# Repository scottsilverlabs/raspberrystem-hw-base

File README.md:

raspberrystem-hw-base
=====================

raspberrySTEM(TM) base hardware schematics and related documents

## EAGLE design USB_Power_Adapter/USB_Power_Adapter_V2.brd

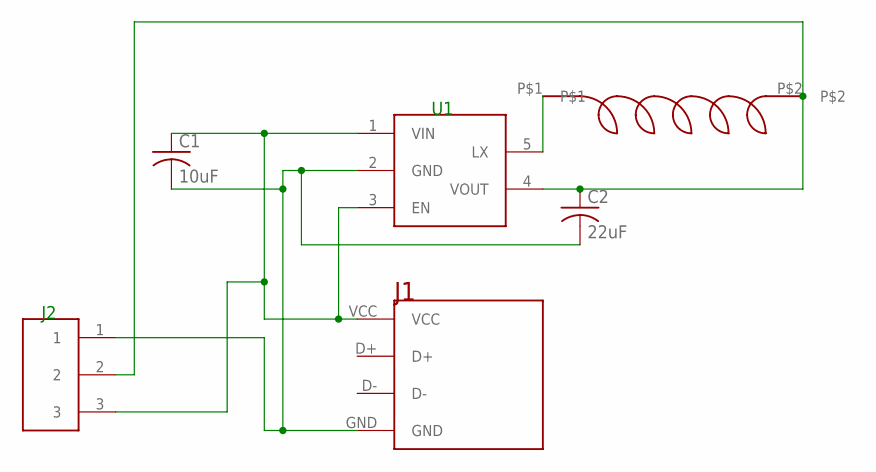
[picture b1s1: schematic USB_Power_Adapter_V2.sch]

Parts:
C1: 10uF; C0805K
C2: 22uF; C0805K
J1: MICROUSBMICROUSB_THRU; MICROUSB_THRU
U1: SC189
U$1: SMDINDUCTOR
U$2: DF3_1X3

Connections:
GND: C1.2, C2.2, J1.GND, U1.2 (GND), U$2.1
L: U1.5 (LX), U$1.P$1
VIN: C1.1, J1.VCC, U1.1 (VIN), U1.3 (EN), U$2.3
VOUT: C2.1, U1.4 (VOUT), U$1.P$2, U$2.2

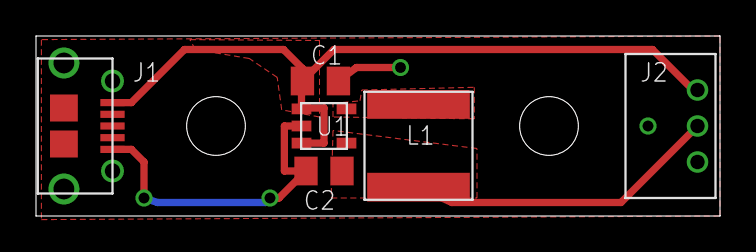
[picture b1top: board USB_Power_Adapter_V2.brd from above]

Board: 2 copper layers, 38.0 x 10.0 mm, 6 parts (0 on the bottom side), 4 nets.

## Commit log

2014-06-06 Added AL License to all applicable files
2014-06-17 Added schematics, gerber files, and BOM for USB Power Adapter
2014-06-18 Initial rev of case (pulled from dropbox rev8 dev)
2014-06-19 Forced name U1
2014-06-19 Fixed junctions
2014-06-25 Updates for new power and connector PCBs, and other fixes
    - Fastex clip broke - reinforce
    - Epilog still has artifact where Battery strap arrows are cut instead
    of just etched
    - Add more space to get battery strap on?
    - Adjust battery strap width? (0.3"?)
    - Move RasPi box etching ~1/64" to the right
2014-06-25 Added mounting holes, changed all screws to 5/8"
2014-06-25 Modified speaker, Lid connector PCB, screws
    Old speaker holes hit speaker diaphragm, new holes shouldn’t
    (untested). Added Custom Lid Connector PCB holes. Changed all screws
    to use #4-40, 5/8”
2014-06-25 Added USB power adapter files
2014-07-07 Added parts library
2014-07-24 Decreased and changed "Battery Strap" font, removed "Breadboards"
2014-07-24 Fixed broken line width/color
2014-07-24 Added new logo and text
2014-07-24 Changed spacing and clearance for USB Power Adapter PCB
2014-07-25 Removed old usb power adapter Gerber files and move L1 text
2014-07-26 Base acrylic: USB power adapter
    Increased USB power adapter top screw hole to oval to accommodate both
    board versions (2 places)
    Removed J from USB power spacer for Model B plus compatibility
2014-07-27 Case: Removed vertical mount
    Vertical mount is a point of failure for the acrylic (especially as
    when mounted, the lid has huge leverage to snap the mount notch). When
    the screw holes are adjusted for Model B+ compatibility, this we be
    even worse. Additionally, it may have little practical use, as the
    case can stand vertically.
    May revisit at a later time.
2014-07-27 Case: widened base feet
    Moved feet to edges of board to make more room for side holes needed
    for Model B+ compatibility.
2014-07-28 Case: Added Blank lid
    Added first cut blank lid, with rubber band straps and mounting holes.
2014-07-28 Case: base additions
    Keyed PCB header. Added vertical elastic band straps.
2014-07-28 Case: Refactored straps
    Made better vertical rubber band straps in base. Changed straps in
    blank lid. Adjusted mounting holes.
2014-07-30 Adjust lid retention clip. New sidewall.
    New sidewall has slightly wider fated clip heads to reduce chance of
    over bending. To be tested.
2014-08-04 Switch back to old style speaker holes, but with more.
    New speakers have a small gasket around the edge lip that prevents the speaker from bumping into
    the acrylic - so the the change to one big hole is not needed. Also added more holes for more
    sound output.
2014-08-07 Acrylic: Added Gamer lid, multiple lid fixes for PCBs
    - Gamer lid
    - PCB connector issues, clearance, keep outs for cables hitting RPi
    - PCB connector for Blank lid, if possible
    - USB power spacer - is length correct?
    - USB power spacer need wider narrow-part of base, and more narrow
    wide-part of base
2014-08-08 Fixed wrong fill on hole
2014-08-08 Final protoype rev
    Full 12x24 panel, 3 full units with lids: gamer, custom, blank
2014-11-07 Added New Parts
2014-12-23 acrylic - Split SVG files into blank/custom/gamer
2014-12-23 Added parts - 2x3 header, 1x6 header
    These parts were being used, but missing from the library. Remade from arbitraily chosen headers
    in main library.
2014-12-29 added missing accelerometer parts
2014-12-29 Added creator parts with new test latch and modified corners
    Modified corners add circle cut to minimize corner stress fractures.
2014-12-29 Redo of speaker bracket
    Speaker bracket screw was hitting breadboard. Speaker bracket was also slightly misaligned from
    the speaker holes. Redid bracket from scratch, made slightly smaller. Untested.
2014-12-29 acrylic - modified corners
    Added circles at corners to minimize corner stress fractures.
2015-01-04 arcylic - Fit new HeaderConnectorBoard
    Increased width of case by 1/4"
2015-01-07 acrylic - Rearranged layout of parts
2015-01-07 acrylic - fix to bottom corner alignment of botton side
2015-01-07 acrylic - Added additonal stress corner cutouts. Other minor adjustments.
2015-01-07 acrylic - removed all etching
    Rationale: etching is too expensive compared to the alternative - stickers -
    which are much more visible and in color.
2015-01-07 acrylic - made mounting holes equidistant from edge
2015-01-07 acrylic - many alignment fixes, especially to left/right sides
2015-01-07 acrylic - added 4 Model A+/B+ holes
2015-01-07 acrylic - First cut Model A/B Plus right side
    Also, modified original Model A/B right side and bottom to be compatible.
2015-01-18 parts - Removed PartsLibrary
    No longer using one master PartsLibrary - now using separate per-board libraries.
2015-01-18 acrylic - Added pop-up to fastex clip. Untested.
2015-01-18 acrylic - increased size of lid edge bump (near fastex)
2015-01-20 acrylic - First new version lab test.
    Removed fastex clip pop-up as it is too delicate. Other minor adjustments.
    Other issues not resolved:
    - Model A/B compatibitity
    - connector board hits Pi.
    - Model A/B Plus compatibitity
    - connector board hits Pi.
2015-01-22 acrylic - increased stress fracture cutout size
    Also, removed Model A/B specific right wall
2015-01-22 acrylic - resized right wall holes and bottom bump
2015-01-22 acrylic - made sidewalls tighter
    Moved sidewall bottom bumpouts 1/32” inwards to make sidewalls fit
    tighter. Untested.
2015-01-22 acrylic - Shrink fastex far left right curves
    Shrinking them to provide little more lateral strength to clips.
2015-01-22 acrylic - moved Pi 0.1" left
    … to prove better alignment of 40pin ribbon cable
2015-01-22 acrylic - accommodated new Lid connector PCB with spacer board
    Untested. Likely requires 1/8” length increase of full unit
2015-01-22 acrylic - Increased overall unit length by 1/8"
    Acommodates lid connecttor board and spacer. Hand tested fit via printouts on
    paper.
2015-01-22 acrylic - many changes/fixes to new Lid connector and spacer board
2015-02-18 acrylic - Removed old brackets, broken grouping, 2 more bushings
2015-02-18 acrylic - Left wall key hole was misaligned
2015-02-18 acrylic - tighter wall key holes
    made narrower, and shifted to push against wall when in the slot
2015-02-18 acrylic - adjust SD cutout
    Allows Model A/B plus to fully access microSD slot (fullsize SD sticks out, so
    it doesn't matter)
2015-02-18 acrylic - shifted orignal Model A/B mounting holes
    They were misaligned with HDMI port hole.
2015-02-18 acrylic - RasPi mounting holes were too small.
2015-02-18 acrylic - strengthened lid lip near fastex
2015-02-18 acrylic - conflict with connector lid screws and header
    Header board will need to have moutning holes adjusted
2015-02-18 acrylic - ajusted RasPi orig mounting holes again
    Better center alignment of HDMI connector
2015-02-18 acrylic - side walls less tight, realign lid holes, adjust lid conn holes
2015-02-18 acrylic - fixed lid connector misalignments
2015-02-19 acrylic - increased feet length 1/16"
    Extra clearance for longer RasPi mounting screws facing down for easier install
2015-02-19 acrylic - readjust fastex lid holes
    clamping of fastex lid hole was too tight (partially caused by tightening the sidewalls)
2015-02-19 acrylic - adjust SD card cutout 1/16" right
2015-02-19 acrylic - move speaker left 1/8"
2015-02-19 acrylic - misaligned lid lip
2015-03-03 acrylic - Changed sidewall screw length to 9/16"
    Now, all screws in the design (4 sidewall, 2 or 4 Pi mount, 4 Lid connector
    mount) can use the same - #4 9/16".
    Also, adjusted cutouts at sidewall screw cutout corners (used for crack
    prevention). They were circle-based, but didn't need to be, and created a too
    complex cut.
2015-03-04 acrylic - added reference 1 inch square
2015-03-04 acrylic - removed bushings
2015-03-18 acrylic - added speaker bracket
2015-03-18 acrylic - duplicated speaker bracket accross sheet
2015-03-23 laser - Added new parts, untested
2015-03-23 acrylic - shrunk lid connector by 1/16" width
    1/32" removed from each side. Now 6 pieces will fit butted together on a 24"
    wide sheet.
2015-03-24 acrylic - divided speaker bracket into 2
    Speaker bracket was being cut in contiguous pairs, but this caused artifacts at
    the edges.
2015-03-24 cardboard - adjusted width, tested in real box
2015-03-24 cardboard - adjusted size, tested in real acrylic
2015-03-24 acrylic - Added logo back in, slightly smaller now.
2015-03-24 acrylic - new laser - widened/lengthened left side alignment holes
    changes for new laser at Potomac Photonics
2015-03-25 acrylic - adjust fastex clip height and width
2015-03-26 acrylic - Redesigned speaker spacer
    New spacer to but cut from 1/16" acrylic (instead of chipboard), and to have
    cutout to adjust to speaker hole size
2015-04-06 acrylic - Converted logo image from raster to vector
    Note - it wasn't importing properly into CorelDraw at Potomac Photonics, but it
    should be a vector anyway.
2015-04-06 acrylic - adjust sidewall clamping to not be so tight
2015-04-07 acrylic - widen fastex clip holes for more entry clearance
2015-04-07 acrylic - Reversed etching on lid
    Etching on backside looks much cleaner - like artistic etched glass which is
    generally done on the back side.
2015-04-07 acrylic - Removed old acrylic versions
2015-04-08 acrylic - Split CREATOR into separate parts sheets.
    All parts laid out in optimal grid, cloned from original in the bottom left
    corner. Sheets are 36x24, compatible with the Potomac Phtonics Epilog laser
    cutter bed.
2015-04-09 acrylic - gamer - Just like creator, except...
    ...with holes, and slightly larger ribbon cable hole.
2015-04-10 acrylic - Merged lids (Gamer & Creator)
    Previously, the gamer lid and creator lid were independent. With the latest
    design, the only difference between the two is that the Gamer requires holes
    for mounting a board on the top, and requires clearance to feed the ribbon
    cable through the lid.
    This design widens the lid connector hole, and adds a grid of 1" spaced
    mounting holes.
2015-04-15 power regulator - Removed deprecated board
2015-04-15 packaging - Generic PCB packaging files used by all boards.
2015-04-15 PCB - Added additional help notes, and make help
2015-04-17 logo - Added Logo in Eagle format, and scaling scripts.
2015-05-01 acrylic - production EPS files
2015-05-05 PCB Makefile - updated procedure comments
2015-05-28 acrylic - tiled clones of spacer, bracket, cardboard
    Also, for cardboard spacer, shrunk width by 1/64", and softened finger pull corners.
2015-05-28 acrylic - added EPS files (bracket, spacer, cardboard)
2015-05-28 foam spacer - increased size
    The laser has a significant kerf with the foam.
2015-06-18 acrylic - lid spacer - converted spaker hole cutout to hole
    ... for better strain relief for solder joints
2015-07-01 acrylic - Updated lid spacer EPS
